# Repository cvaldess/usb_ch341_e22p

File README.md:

# usb_ch341_e22p

Adaptador **USB → SPI** para usar un módulo LoRa **EBYTE E22P-868M30S** (SX1262 + PA, 30 dBm / 1 W) con **[meshtasticd](https://meshtastic.org/docs/software/linux/)** en un PC o una Raspberry Pi, sin necesidad de GPIO.

El puente es un **CH341F** en modo UIO, que es el que soporta el driver [`libch341-spi-userspace`](https://github.com/meshtastic/libch341-spi-userspace) de Meshtastic. Un multiplexor **TPS2115A** conmuta automáticamente entre la alimentación del USB y la de un jack DC, de modo que el módulo puede transmitir a plena potencia sin sobrecargar el puerto del ordenador.

---

## Especificaciones

| | |
|---|---|
| PCB | 49,22 × 63,54 mm · **2 capas** · 1,6 mm · vías 0,6/0,3 mm |
| Puente USB | CH341F (QFN-28), modo paralelo/síncrono (PID `0x5512`) |
| Radio | EBYTE E22P-868M30S — SX1262 + PA, hasta **30 dBm**, 868 MHz |
| Alimentación | USB-C 5 V **o** jack DC 5 V (2,5 mm), conmutación automática |
| Límite de corriente | 1,28 A nominal (TPS2115A con `R8` = 390 Ω) |
| Lógica | 3,3 V (LDO XC6206), nivel del E22P |
| Antena | SMA hembra acodada, 50 Ω |
| Configuración | EEPROM 24C02 para VID/PID/modo |

## Cómo funciona la alimentación

Es la parte menos obvia del diseño. El E22P consume **600–670 mA transmitiendo a 30 dBm**, más de lo que un puerto USB garantiza (500 mA). La placa resuelve esto con un multiplexor cuya selección es **determinista**, no por comparación de tensiones:

| USB | Jack | `D1` | `D0` | Fuente activa | LED `D4` |
|:---:|:----:|:----:|:----:|---|:---:|
| ✅ | ❌ | 0 | 0 | **USB** — usar potencia reducida | apagado |
| ✅ | ✅ | 1 | 0 | **Jack** — plena potencia | **encendido** |
| ❌ | ✅ | 0 | 0 | ninguna (Hi-Z) | — |
| ❌ | ❌ | 0 | 0 | ninguna (Hi-Z) | — |

`D0` está fijo a masa y `D1` lo gobierna el contacto de conmutación del jack, con `R7` (10 kΩ) referenciado a **VBUS**. Así `D1` codifica *«hay jack **y** hay USB»*, y de ahí salen dos propiedades útiles:

- Con el jack puesto **siempre manda el jack**, independientemente de qué fuente tenga más tensión (las dos filas útiles usan `D0`=0, donde la tabla de verdad del TPS2115A ignora la comparación `IN2>IN1`).
- **Sin USB el módulo queda sin alimentar**, que es lo que se quiere: la placa no sirve de nada desconectada del host, y así se evita que el E22P alimentado inyecte corriente por los pines del CH341 apagado.

El LED `D4` cuelga de `STAT`, que es open-drain y se pone a nivel bajo cuando `IN1` está activo: **encendido = alimentándose del jack**.

## Configuración de meshtasticd

Los pines del CH341 se numeran como líneas UIO `D0`–`D7`. El mapeo de esta placa coincide con el preset oficial `lora-usb-meshtoad-e22.yaml`:

```yaml
Lora:
  Module: sx1262
  CS: 0        # D0 · pin 15 → NSS
  RXen: 1      # D1 · pin 16 → EN   (habilitación del front-end RF)
  Reset: 2     # D2 · pin 17 → NRST
  Busy: 4      # D4 · pin 19 → BUSY
  IRQ: 6       # D6 · pin 21 → DIO1
  spidev: ch341
  DIO2_AS_RF_SWITCH: true
  DIO3_TCXO_VOLTAGE: true
  USB_VID: 0x1A86
  USB_PID: 0x5512
  # Alimentando SÓLO por USB, baja la potencia para no sobrecargar el puerto:
  # SX126X_MAX_POWER: 10
```

`SCK` va en `D3` (pin 18) y `MOSI` en `D5` (pin 20); `MISO` está en `D7` (pin 22), que junto con `D6` es entrada fija en el CH341. `DIO2_AS_RF_SWITCH` es obligatorio: en la placa el pin `DIO2` está puenteado a `T/R CTRL`, tal como indica la nota ① del manual de EBYTE.

> [!IMPORTANT]
> **La EEPROM `U2` debe estar programada** con `MODE = 0x12` para que el CH341 enumere como puerto paralelo/síncrono. Sin programar, el chip lee `SDA`/`SCL` flotantes y arranca como **puerto serie**, no como SPI. Se graba por USB con `CH341CFG` o `IMSProg`.

## Fabricación

Todo lo necesario está en [`fab/`](fab/):

| Archivo | Para qué |
|---|---|
| `gerbers-jlcpcb.zip` | Gerbers + taladros, listo para subir |
| `bom-jlcpcb.csv` | Lista de materiales |
| `cpl-jlcpcb.csv` | Posiciones para montaje |
| `*.gtp` / `*.gbp` | Capas de pasta, por si pides esténcil |

Parámetros: **2 capas, 1,6 mm, HASL o ENIG**. Nada fuera de las capacidades estándar.

### Notas sobre el BOM

- **`U3` (E22P-868M30S) y `SMA1` no tienen código LCSC**: el módulo se compra en EBYTE o en AliExpress, y el conector SMA es genérico. Ambos se sueldan aparte.
- **Los pasivos genéricos no llevan código asignado** (100 nF, 1 µF, 10 µF, y las resistencias). Son valores de stock básico y conviene dejar que el fabricante los elija de su inventario.

## Componentes principales

| Ref | Componente | Función |
|---|---|---|
| `U1` | CH341F | Puente USB ↔ SPI |
| `U2` | 24C02 | EEPROM de configuración (VID/PID/modo) |
| `U3` | E22P-868M30S | Módulo LoRa SX1262 + PA |
| `U4` | XC6206P332MR | LDO 3,3 V para el CH341 |
| `U5` | TPS2115A | Multiplexor de alimentación |
| `U6` | DC-005-2.5A | Jack DC 5 V con contacto de conmutación |
| `U7` | H7VHD3UA | TVS de protección en VBUS |
| `D2` | TPD4E05U06 | Protección ESD del USB (D+/D−/CC1/CC2) |
| `C5` | 470 µF / 16 V | Polímero sólido, 28 mΩ ESR — reserva para los picos de TX |

## Datasheets

No se incluyen los PDF en el repositorio (son material con derechos de sus fabricantes). Enlaces a las fuentes:

- [CH341 (WCH)](https://www.wch-ic.com/products/CH341.html) · [E22P-868M30S (EBYTE)](https://www.cdebyte.com/products/E22P-868M30S) · [TPS2115A (TI)](https://www.ti.com/product/TPS2115A) · [TPD4E05U06 (TI)](https://www.ti.com/product/TPD4E05U06) · [XC6206 (Torex)](https://www.torexsemi.com/products/voltage-regulators/xc6206/)
- Referencias LCSC: `C412870` (CH341F) · `C2863458` (TPS2115A) · `C138714` (TPD4E05U06) · `C20615807` (H7VHD3UA) · `C709357` (USB-C) · `C2880544` (jack) · `C9002` (cristal)

## Limitaciones conocidas

- **Sin protección en la entrada del jack.** No hay TVS ni protección de polaridad inversa en `IN1`. El E22P se daña por encima de 5,5 V y el TPS2115A tiene un máximo absoluto de 6 V: un alimentador de 9 o 12 V, o de centro negativo, destruye ambos. **Usa sólo 5 V y comprueba la polaridad.**
- **La potencia de transmisión no se detecta sola.** meshtasticd no sabe si el jack está puesto, así que `SX126X_MAX_POWER` es un ajuste fijo. Si vas a usar la placa sólo por USB, bájalo.

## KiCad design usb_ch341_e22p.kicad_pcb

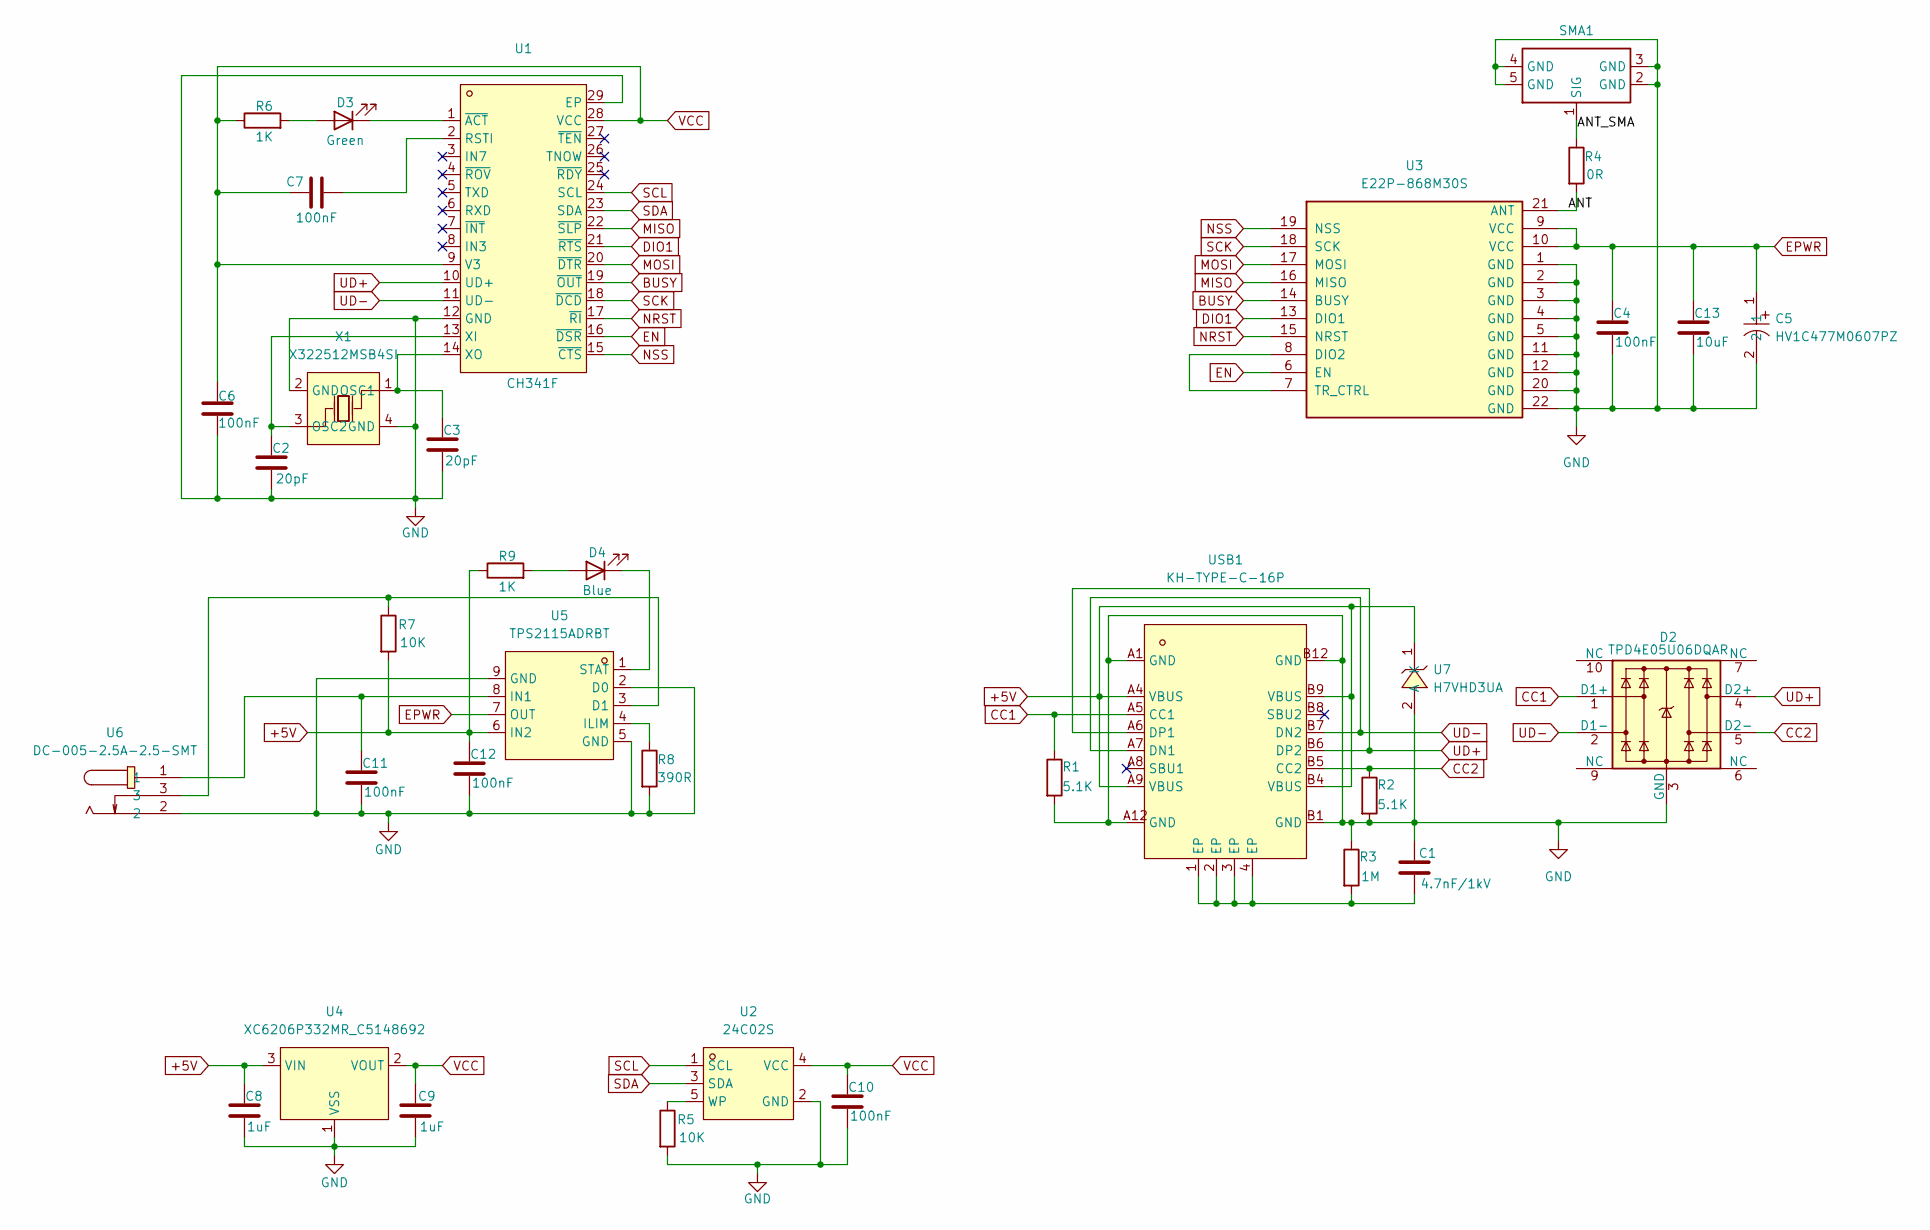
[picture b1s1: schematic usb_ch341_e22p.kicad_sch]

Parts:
C1: 4.7nF/1kV; C_1206_3216Metric; LCSC Part C9192
C2, C3: 20pF; C_0402_1005Metric; LCSC Part C5137579
C4, C6, C7, C10, C11, C12: 100nF; C_0603_1608Metric
C5: HV1C477M0607PZ; CAP-SMD_BD6.3-L6.6-W6.6-LS7.8-FD; MPN HV1C477M0607PZ; LCSC Part C42436549
C8, C9: 1uF; C_0603_1608Metric
C13: 10uF; C_0603_1608Metric
D2: TPD4E05U06DQAR; USON-10_L2.5-W1.0-P0.50-BL; MPN TPD4E05U06DQAR; LCSC Part C138714
D3: Green; LED_0603_1608Metric; LCSC Part C7371903
D4: Blue; LED_0603_1608Metric; LCSC Part C7371903
R1, R2: 5.1K; R_0603_1608Metric
R3: 1M; R_0603_1608Metric
R4: 0R; R_0603_1608Metric
R5, R7: 10K; R_0603_1608Metric
R6, R9: 1K; R_0603_1608Metric
R8: 390R; R_0603_1608Metric
SMA1: -; SMA-TH_HJ-SMA175; Manufacturer Part HJ-SMA175; LCSC Part Name 两件套 内孔 SMA 弯头
U1: CH341F; QFN-28_L4.0-W4.0-P0.40-BL-EP; MPN CH341F; LCSC Part C412870
U2: 24C02S; SOT-23-5_L3.0-W1.6-P0.95-LS2.8-BR; MPN 24C02S(XBLW); LCSC Part C18723540
U3: E22P-868M30S; PE22(900M30S); MPN E22P-868M30S
U4: XC6206P332MR_C5148692; SOT-23-3_L2.9-W1.3-P1.90-LS2.4-BR; MPN XC6206P332MR; LCSC Part C5148692
U5: TPS2115ADRBT; SON-8_L3.0-W3.0-P0.65-TL-EP; MPN TPS2115ADRBT; LCSC Part C2863458
U6: DC-005-2.5A-2.5-SMT; DC-IN-TH_XKB_DC-005-2.5A-2.5-SMT; MPN DC-005-2.5A-2.5-SMT; LCSC Part C2880544
U7: H7VHD3UA; SOD-323_L1.7-W1.3-LS2.7-RD; MPN H7VHD3UA; LCSC Part C20615807
USB1: KH-TYPE-C-16P; USB-C-SMD_KH-TYPE-C-16P; MPN KH-TYPE-C-16P; LCSC Part C709357
X1: X322512MSB4SI; CRYSTAL-SMD_4P-L3.2-W2.5-BL; MPN X322512MSB4SI; LCSC Part C9002

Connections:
+5V: C8.1, C12.1, R7.2, R9.1, U4.3 (VIN), U5.6 (IN2), U7.1 (K), USB1.A4 (VBUS), USB1.A9 (VBUS), USB1.B4 (VBUS), USB1.B9 (VBUS)
/ANT: R4.2, U3.21 (ANT)
/ANT_SMA: R4.1, SMA1.1 (SIG)
BUSY: U1.19 (~OUT), U3.14 (BUSY)
CC1: D2.1 (D1+), R1.1, USB1.A5 (CC1)
CC2: D2.5 (D2-), R2.1, USB1.B5 (CC2)
DIO1: U1.21 (~RTS), U3.13 (DIO1)
EN: U1.16 (~DSR), U3.6 (EN)
EPWR: C4.1, C5.1, C13.1, U3.9 (VCC), U3.10 (VCC), U5.7 (OUT)
GND: C1.1, C2.2, C3.2, C4.2, C5.2, C6.2, C8.2, C9.2, C10.2, C11.2, C12.2, C13.2, D2.3 (GND), D2.8 (GND), R1.2, R2.2, R3.1, R5.2, R8.2, SMA1.2 (GND), SMA1.3 (GND), SMA1.4 (GND), SMA1.5 (GND), U1.12 (GND), U1.29 (EP), U2.2 (GND), U3.1 (GND), U3.2 (GND), U3.3 (GND), U3.4 (GND), U3.5 (GND), U3.11 (GND), U3.12 (GND), U3.20 (GND), U3.22 (GND), U4.1 (VSS), U5.2 (D0), U5.5 (GND), U5.9 (GND), U6.2, U7.2 (A), USB1.A1 (GND), USB1.A12 (GND), USB1.B1 (GND), USB1.B12 (GND), X1.2 (GND), X1.4 (GND)
MISO: U1.22 (~SLP), U3.16 (MISO)
MOSI: U1.20 (~DTR), U3.17 (MOSI)
NRST: U1.17 (~RI), U3.15 (NRST)
NSS: U1.15 (~CTS), U3.19 (NSS)
unnamed: C1.2, R3.2, USB1.1 (EP), USB1.2 (EP), USB1.3 (EP), USB1.4 (EP)
unnamed: D3.2 (A), R6.2
unnamed: D3.1 (K), U1.1 (~ACT)
unnamed: D4.2 (A), R9.2
unnamed: D4.1 (K), U5.1 (STAT)
unnamed: C7.1, U1.2 (RSTI)
unnamed: C2.1, U1.13 (XI), X1.3 (OSC2)
unnamed: C3.1, U1.14 (XO), X1.1 (OSC1)
unnamed: R5.1, U2.5 (WP)
unnamed: U3.7 (TR_CTRL), U3.8 (DIO2)
unnamed: R7.1, U5.3 (D1), U6.3
unnamed: R8.1, U5.4 (ILIM)
unnamed: C11.1, U5.8 (IN1), U6.1
SCK: U1.18 (~DCD), U3.18 (SCK)
SCL: U1.24 (SCL), U2.1 (SCL)
SDA: U1.23 (SDA), U2.3 (SDA)
UD+: D2.4 (D2+), U1.10 (UD+), USB1.A6 (DP1), USB1.B6 (DP2)
UD-: D2.2 (D1-), U1.11 (UD-), USB1.A7 (DN1), USB1.B7 (DN2)
VCC: C6.1, C7.2, C9.1, C10.1, R6.1, U1.9 (V3), U1.28 (VCC), U2.4 (VCC), U4.2 (VOUT)

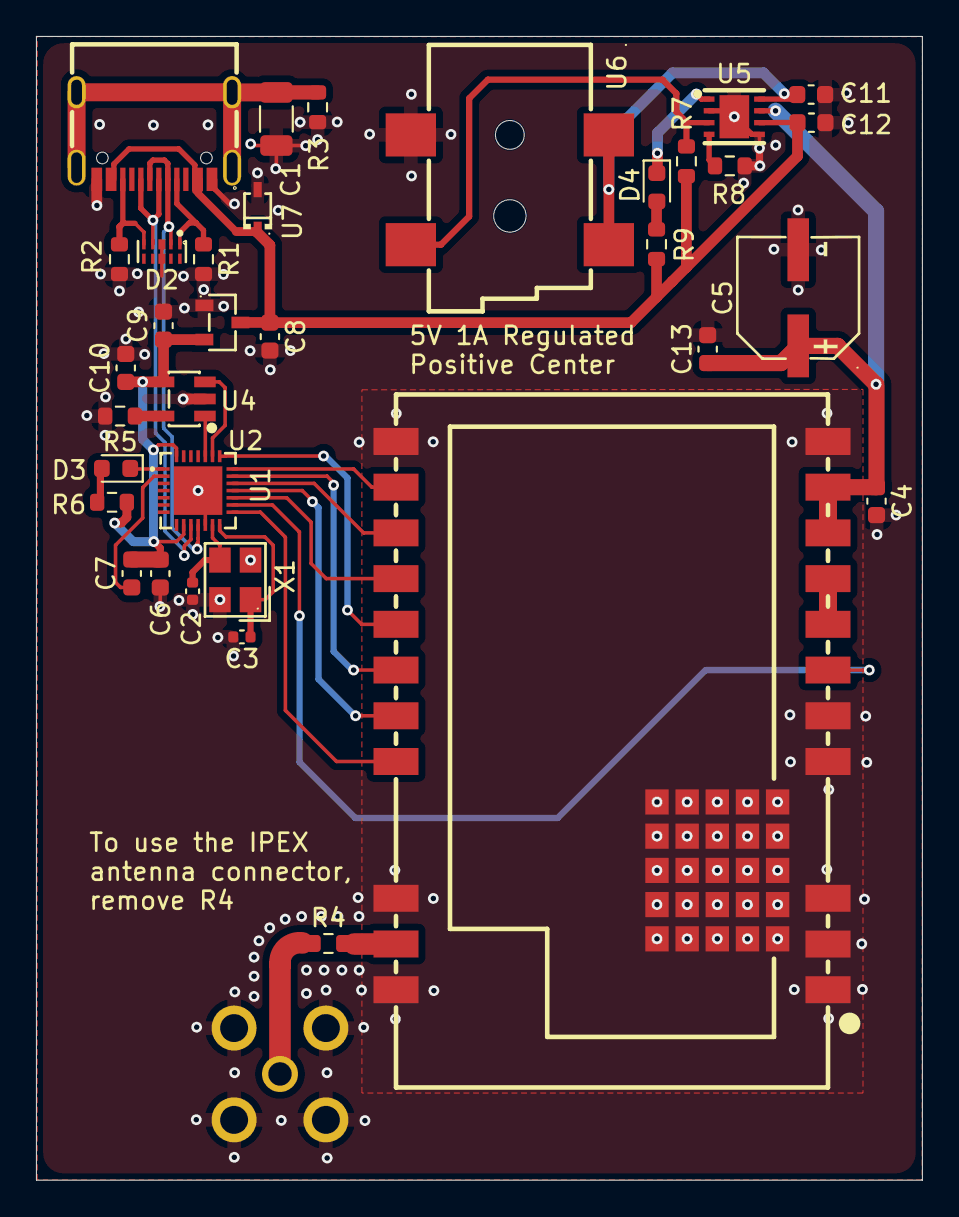
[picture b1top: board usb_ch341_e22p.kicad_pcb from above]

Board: 2 copper layers, 49.2 x 63.5 mm, 35 parts (0 on the bottom side), 33 nets.
